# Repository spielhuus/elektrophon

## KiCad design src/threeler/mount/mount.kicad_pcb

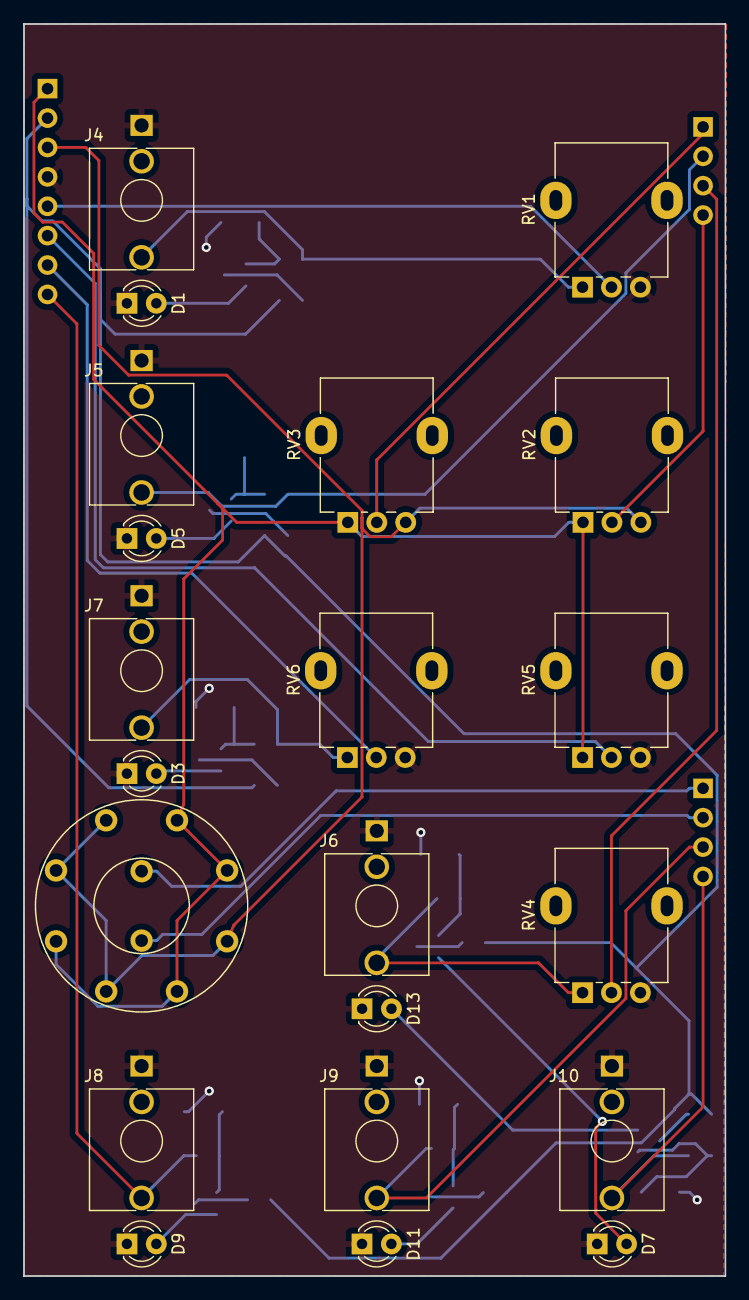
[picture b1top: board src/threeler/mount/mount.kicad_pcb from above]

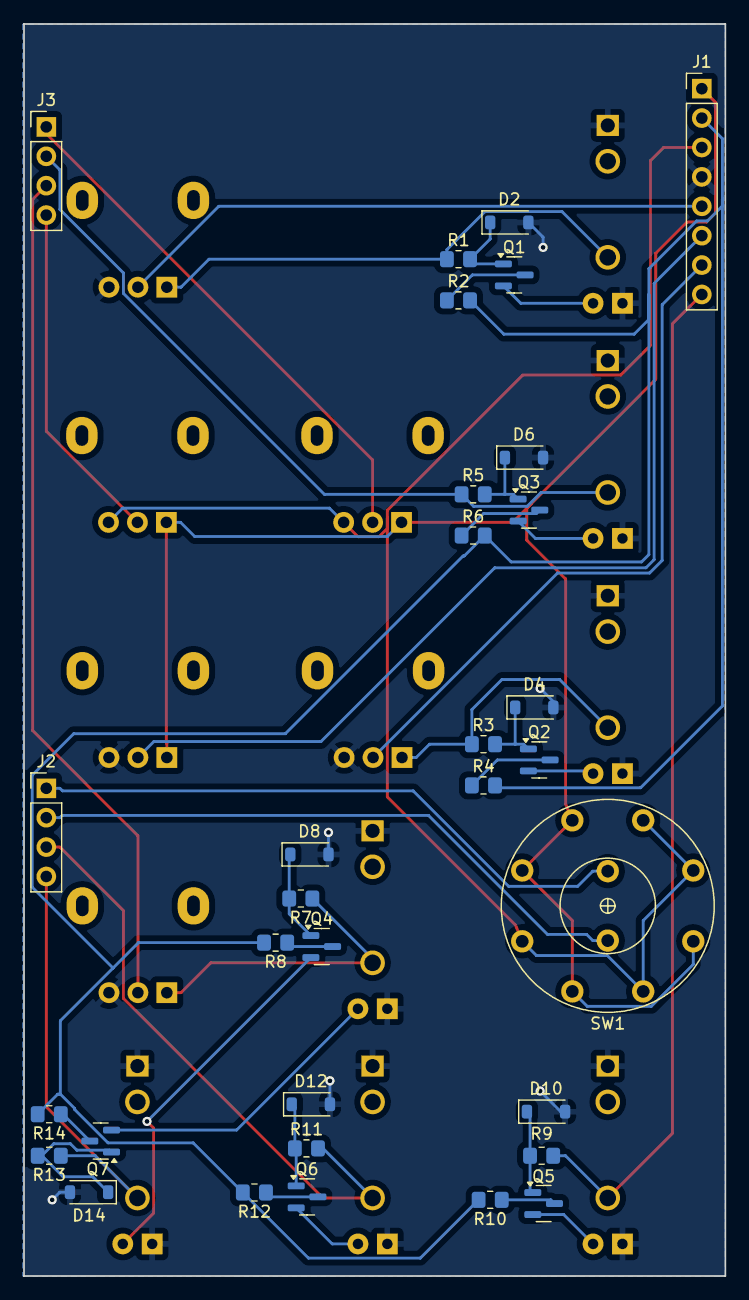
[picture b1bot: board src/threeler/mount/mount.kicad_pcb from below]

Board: 2 copper layers, 60.6 x 108.2 mm, 52 parts (31 on the bottom side), 40 nets.

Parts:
D1: LED (green); LED_D3.0mm
D2, D4, D6, D8, D10, D12, D14: 1N4148W; D_SOD-123
D3, D5, D7: LED (yellow); LED_D3.0mm
D9, D11, D13: LED (red); LED_D3.0mm
J1: Connector; PinHeader_1x08_P2.54mm_Vertical
J2, J3: Connector; PinHeader_1x04_P2.54mm_Vertical
J4, J5, J7: IN; Jack_3.5mm_WQP-PJ398SM_Vertical
J6: FM; Jack_3.5mm_WQP-PJ398SM_Vertical
J8, J9, J10: OUT; Jack_3.5mm_WQP-PJ398SM_Vertical
Q1, Q2, Q3, Q4, Q5, Q6, Q7: MMBT3904; SOT-23
R1, R3, R5, R7, R9, R11, R13: 100k; R_0805_2012Metric_Pad1.20x1.40mm_HandSolder
R2, R4, R6, R8, R10, R12, R14: 5.1k; R_0805_2012Metric_Pad1.20x1.40mm_HandSolder
RV1, RV2, RV3, RV4, RV5, RV6: 100k; Potentiometer_Alpha_RD901F-40-00D_Single_Vertical
SW1: 2P4T; 2P4T.MINI

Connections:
+5V: J1.2, R2.2, R4.2, R6.2, R8.2, R10.2, R12.2, R14.2
+15V: J1.1, RV2.1, RV3.1, RV5.1, SW1.2 (1), SW1.3 (2), SW1.7 (5), SW1.9 (7)
-15V: J1.3, RV2.3, RV3.3, SW1.4 (3), SW1.5 (4), SW1.8 (6), SW1.10 (8)
/A0: J2.1, SW1.1 (A)
/A1: J2.2, SW1.6 (B)
/COARSE: J3.4, RV2.2
/FINE: J3.1, RV3.2
/FM: J3.3, RV4.2
/FM_JACK: J6.T, R7.1, RV4.1
/IN: J1.5, RV1.2
/IN_JACK: J4.T, R1.1, RV1.1
/OUT_1: J1.8, J8.T, R9.1
/OUT_2: J2.3, J9.T, R11.1
/OUT_3: J2.4, J10.T, R13.1
/RES: J1.6, RV5.2
/RES_MOD: J1.7, RV6.2
/RES_MOD_JACK: J7.T, R3.1, RV6.1
/V/O: J3.2, J5.T, R5.1
GND: D1.1 (K), D2.2 (A), D3.1 (K), D4.2 (A), D5.1 (K), D6.2 (A), D7.1 (K), D8.2 (A), D9.1 (K), D10.2 (A), D11.1 (K), D12.2 (A), D13.1 (K), D14.2 (A), J1.4, J4.S, J5.S, J6.S, J7.S, J8.S, J9.S, J10.S, RV1.3, RV4.3, RV5.3, RV6.3
unnamed: D1.2 (A), Q1.2 (E)
unnamed: D2.1 (K), Q1.1 (B), R1.2
unnamed: D3.2 (A), Q2.2 (E)
unnamed: D4.1 (K), Q2.1 (B), R3.2
unnamed: D5.2 (A), Q3.2 (E)
unnamed: D6.1 (K), Q3.1 (B), R5.2
unnamed: D7.2 (A), Q4.2 (E)
unnamed: D8.1 (K), Q4.1 (B), R7.2
unnamed: D9.2 (A), Q5.2 (E)
unnamed: D10.1 (K), Q5.1 (B), R9.2
unnamed: D11.2 (A), Q6.2 (E)
unnamed: D12.1 (K), Q6.1 (B), R11.2
unnamed: D13.2 (A), Q7.2 (E)
unnamed: D14.1 (K), Q7.1 (B), R13.2
unnamed: Q1.3 (C), R2.1
unnamed: Q2.3 (C), R4.1
unnamed: Q3.3 (C), R6.1
unnamed: Q4.3 (C), R8.1
unnamed: Q5.3 (C), R10.1
unnamed: Q6.3 (C), R12.1
unnamed: Q7.3 (C), R14.1

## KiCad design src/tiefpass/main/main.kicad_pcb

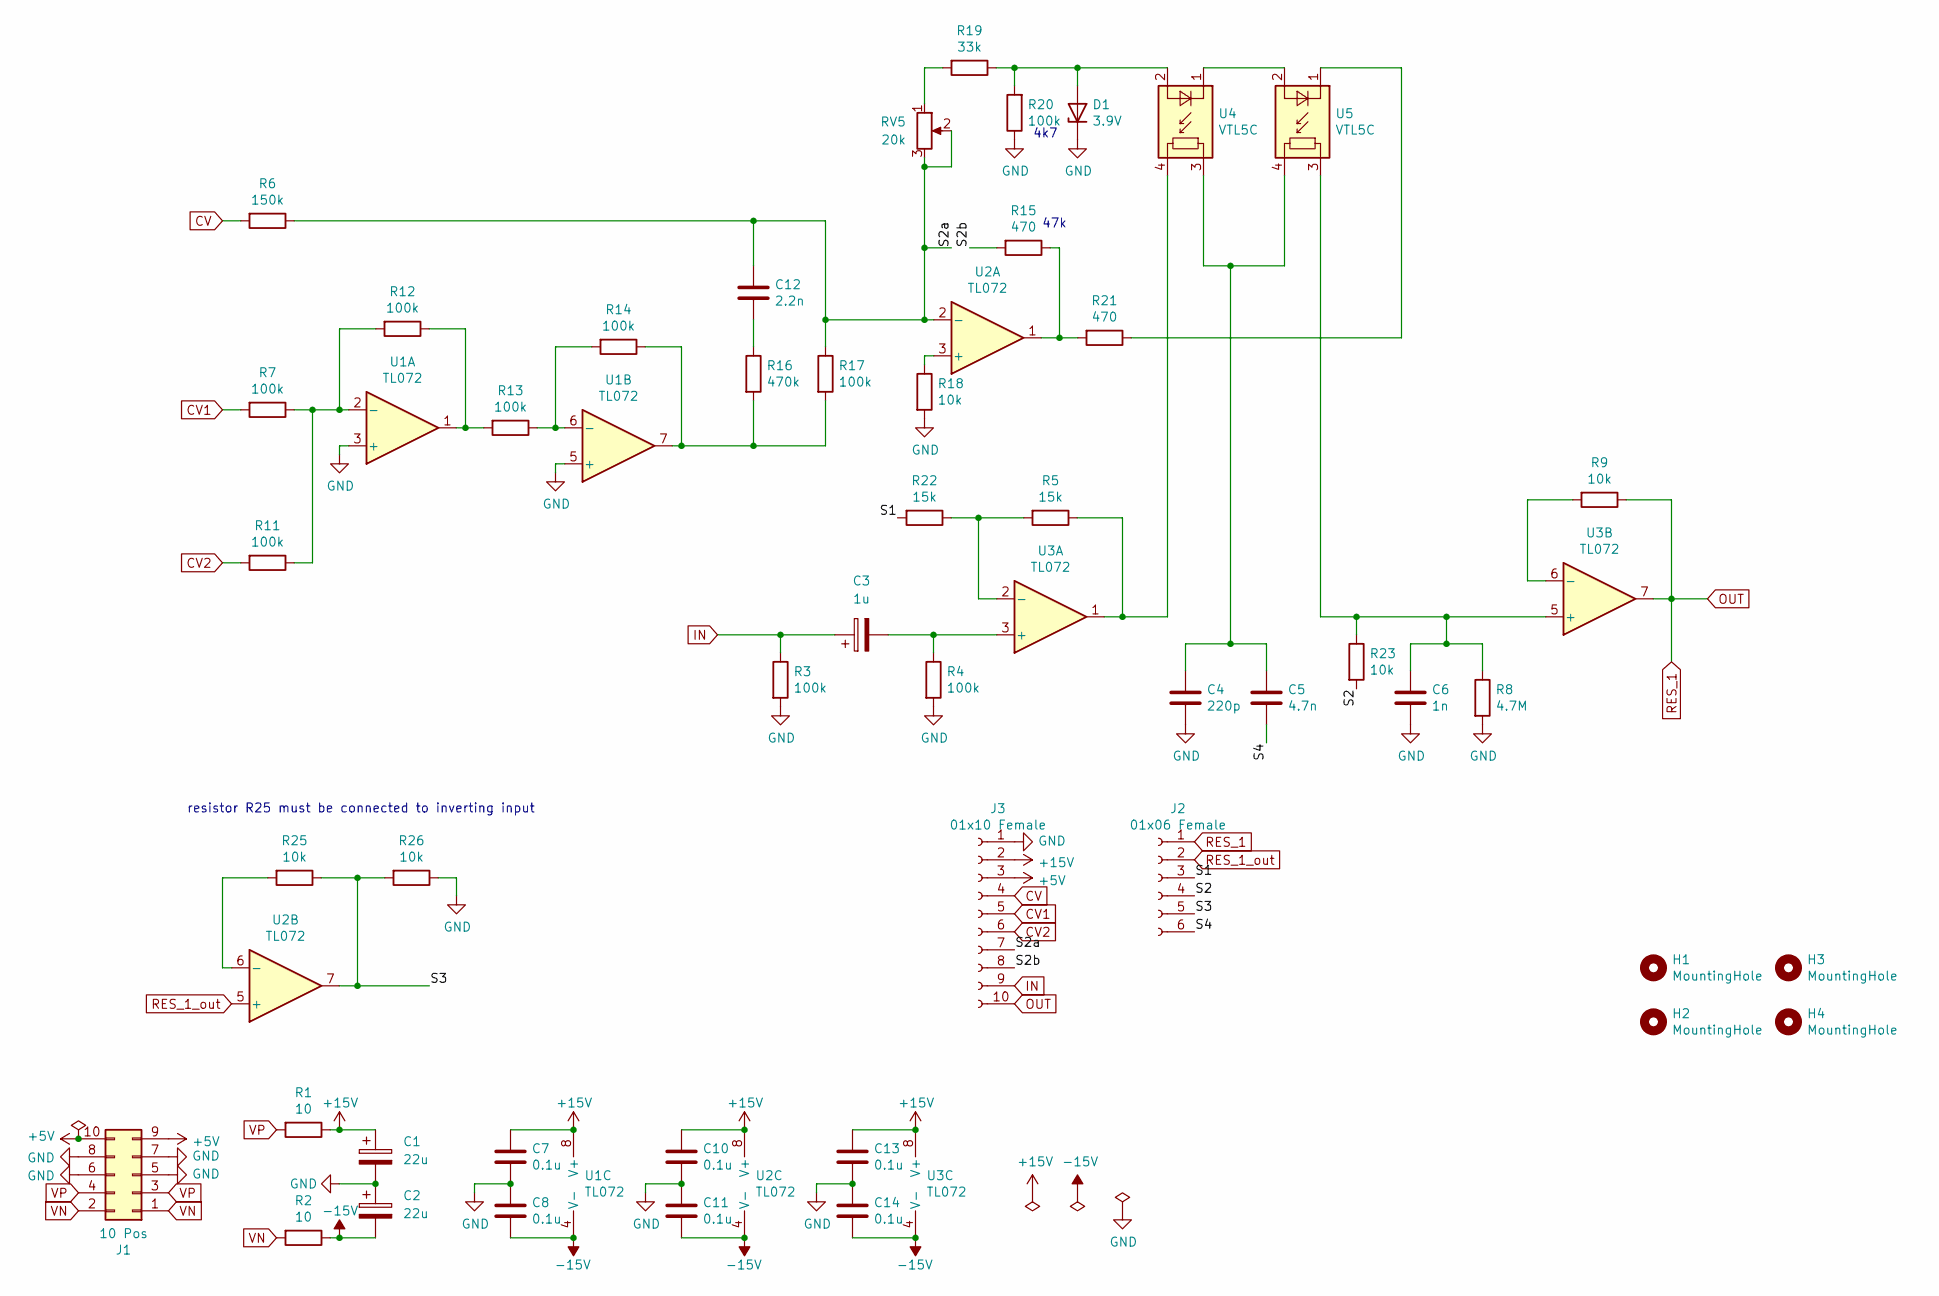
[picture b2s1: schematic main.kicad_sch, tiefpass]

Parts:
C1, C2: 22u; CP_Radial_D6.3mm_P2.50mm
C3: 1u; CP_Radial_D6.3mm_P2.50mm
C4: 220p; C_Rect_L7.2mm_W4.5mm_P5.00mm_FKS2_FKP2_MKS2_MKP2
C5: 4.7n; C_Rect_L7.2mm_W5.5mm_P5.00mm_FKS2_FKP2_MKS2_MKP2
C6: 1n; C_Rect_L7.2mm_W4.5mm_P5.00mm_FKS2_FKP2_MKS2_MKP2
C7, C8, C10, C11, C13, C14: 0.1u; C_Disc_D3.4mm_W2.1mm_P2.50mm
C12: 2.2n; C_Rect_L7.2mm_W4.5mm_P5.00mm_FKS2_FKP2_MKS2_MKP2
D1: 3.9V; D_DO-35_SOD27_P7.62mm_Horizontal
H1, H2, H3, H4: MountingHole; MountingHole_2.2mm_M2
J1: 10 Pos; IDC-Header_2x05_P2.54mm_Vertical
J2: 01x06 Female; PinSocket_1x06_P2.54mm_Vertical
J3: 01x10 Female; PinSocket_1x10_P2.54mm_Vertical
R1, R2: 10; R_Axial_DIN0204_L3.6mm_D1.6mm_P5.08mm_Horizontal
R3, R4, R7, R11, R12, R13, R14, R17, R20: 100k; R_Axial_DIN0204_L3.6mm_D1.6mm_P5.08mm_Horizontal
R5, R22: 15k; R_Axial_DIN0204_L3.6mm_D1.6mm_P5.08mm_Horizontal
R6: 150k; R_Axial_DIN0204_L3.6mm_D1.6mm_P5.08mm_Horizontal
R8: 4.7M; R_Axial_DIN0204_L3.6mm_D1.6mm_P5.08mm_Horizontal
R9, R18, R23, R25, R26: 10k; R_Axial_DIN0204_L3.6mm_D1.6mm_P5.08mm_Horizontal
R15, R21: 470; R_Axial_DIN0204_L3.6mm_D1.6mm_P5.08mm_Horizontal
R16: 470k; R_Axial_DIN0204_L3.6mm_D1.6mm_P5.08mm_Horizontal
R19: 33k; R_Axial_DIN0204_L3.6mm_D1.6mm_P5.08mm_Horizontal
RV5: 20k
U1, U2, U3: TL072; DIP-8_W7.62mm_Socket
U4, U5: VTL5C; PerkinElmer_VTL5C

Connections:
+5V: J1.9, J1.10, J3.3
+15V: C1.1, C7.1, C10.1, C13.1, J3.2, R1.1, U1.8 (V+), U2.8 (V+), U3.8 (V+)
-15V: C2.2, C8.2, C11.2, C14.2, R2.1, U1.4 (V-), U2.4 (V-), U3.4 (V-)
/S1: J2.3, R22.2
/S2: J2.4, R23.2
/S2a: C12.1, J3.7, R6.1, R17.1, RV5.2, RV5.3, U2.2 (-)
/S2b: J3.8, R15.2
/S3: J2.5, R25.1, R26.2, U2.7
/S4: C5.2, J2.6
CV: J3.4, R6.2
CV1: J3.5, R7.2
CV2: J3.6, R11.2
GND: C1.2, C2.1, C4.2, C6.2, C7.2, C8.1, C10.2, C11.1, C13.2, C14.1, D1.1 (K), J1.5, J1.6, J1.7, J1.8, J3.1, R3.2, R4.2, R8.2, R18.2, R20.1, R26.1, U1.3 (+), U1.5 (+)
IN: C3.1, J3.9, R3.1
unnamed: C3.2, R4.1, U3.3 (+)
unnamed: C4.1, C5.1, U4.3, U5.4
unnamed: C6.1, R8.1, R23.1, U3.5 (+), U5.3
unnamed: C12.2, R16.1
unnamed: D1.2 (A), R19.1, R20.2, U4.2 (+)
unnamed: R5.1, U3.1, U4.4
unnamed: R9.2, U3.6 (-)
unnamed: R7.1, R11.1, R12.2, U1.2 (-)
unnamed: R12.1, R13.2, U1.1
unnamed: R13.1, R14.2, U1.6 (-)
unnamed: R14.1, R16.2, R17.2, U1.7
unnamed: R15.1, R21.2, U2.1
unnamed: R18.1, U2.3 (+)
unnamed: R19.2, RV5.1
unnamed: R21.1, U5.1 (-)
unnamed: R5.2, R22.1, U3.2 (-)
unnamed: R25.2, U2.6 (-)
unnamed: U4.1 (-), U5.2 (+)
OUT: J2.1, J3.10, R9.1, U3.7
RES_1_out: J2.2, U2.5 (+)
VN: J1.1, J1.2, R2.2
VP: J1.3, J1.4, R1.2

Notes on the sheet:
resistor R25 must be connected to inverting input
47k
4k7

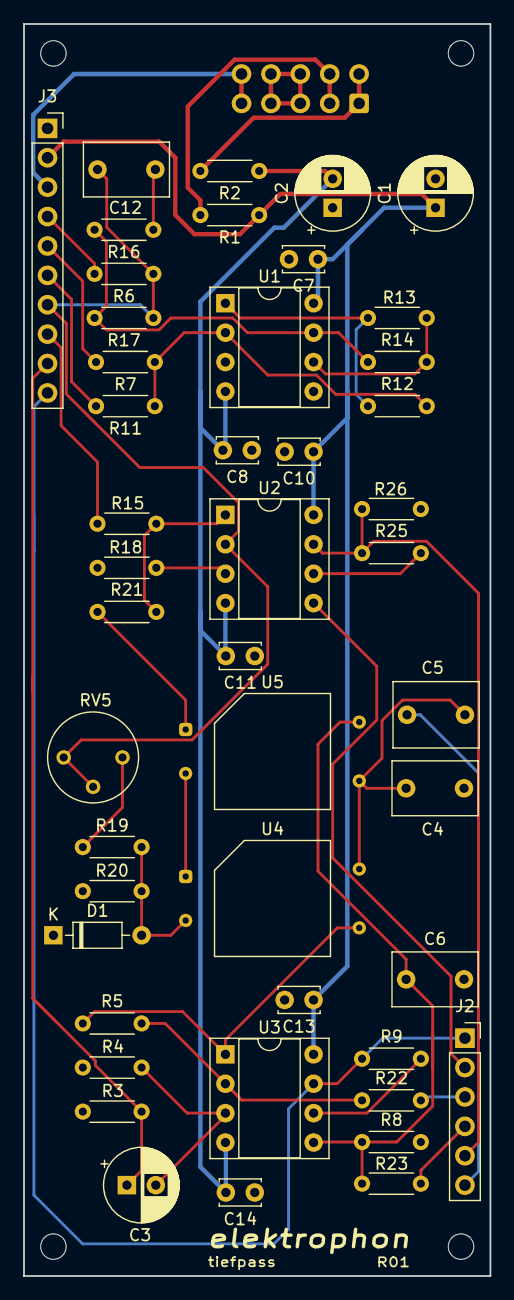
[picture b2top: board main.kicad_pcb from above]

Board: 2 copper layers, 40.3 x 108.2 mm, 51 parts (1 on the bottom side), 36 nets.

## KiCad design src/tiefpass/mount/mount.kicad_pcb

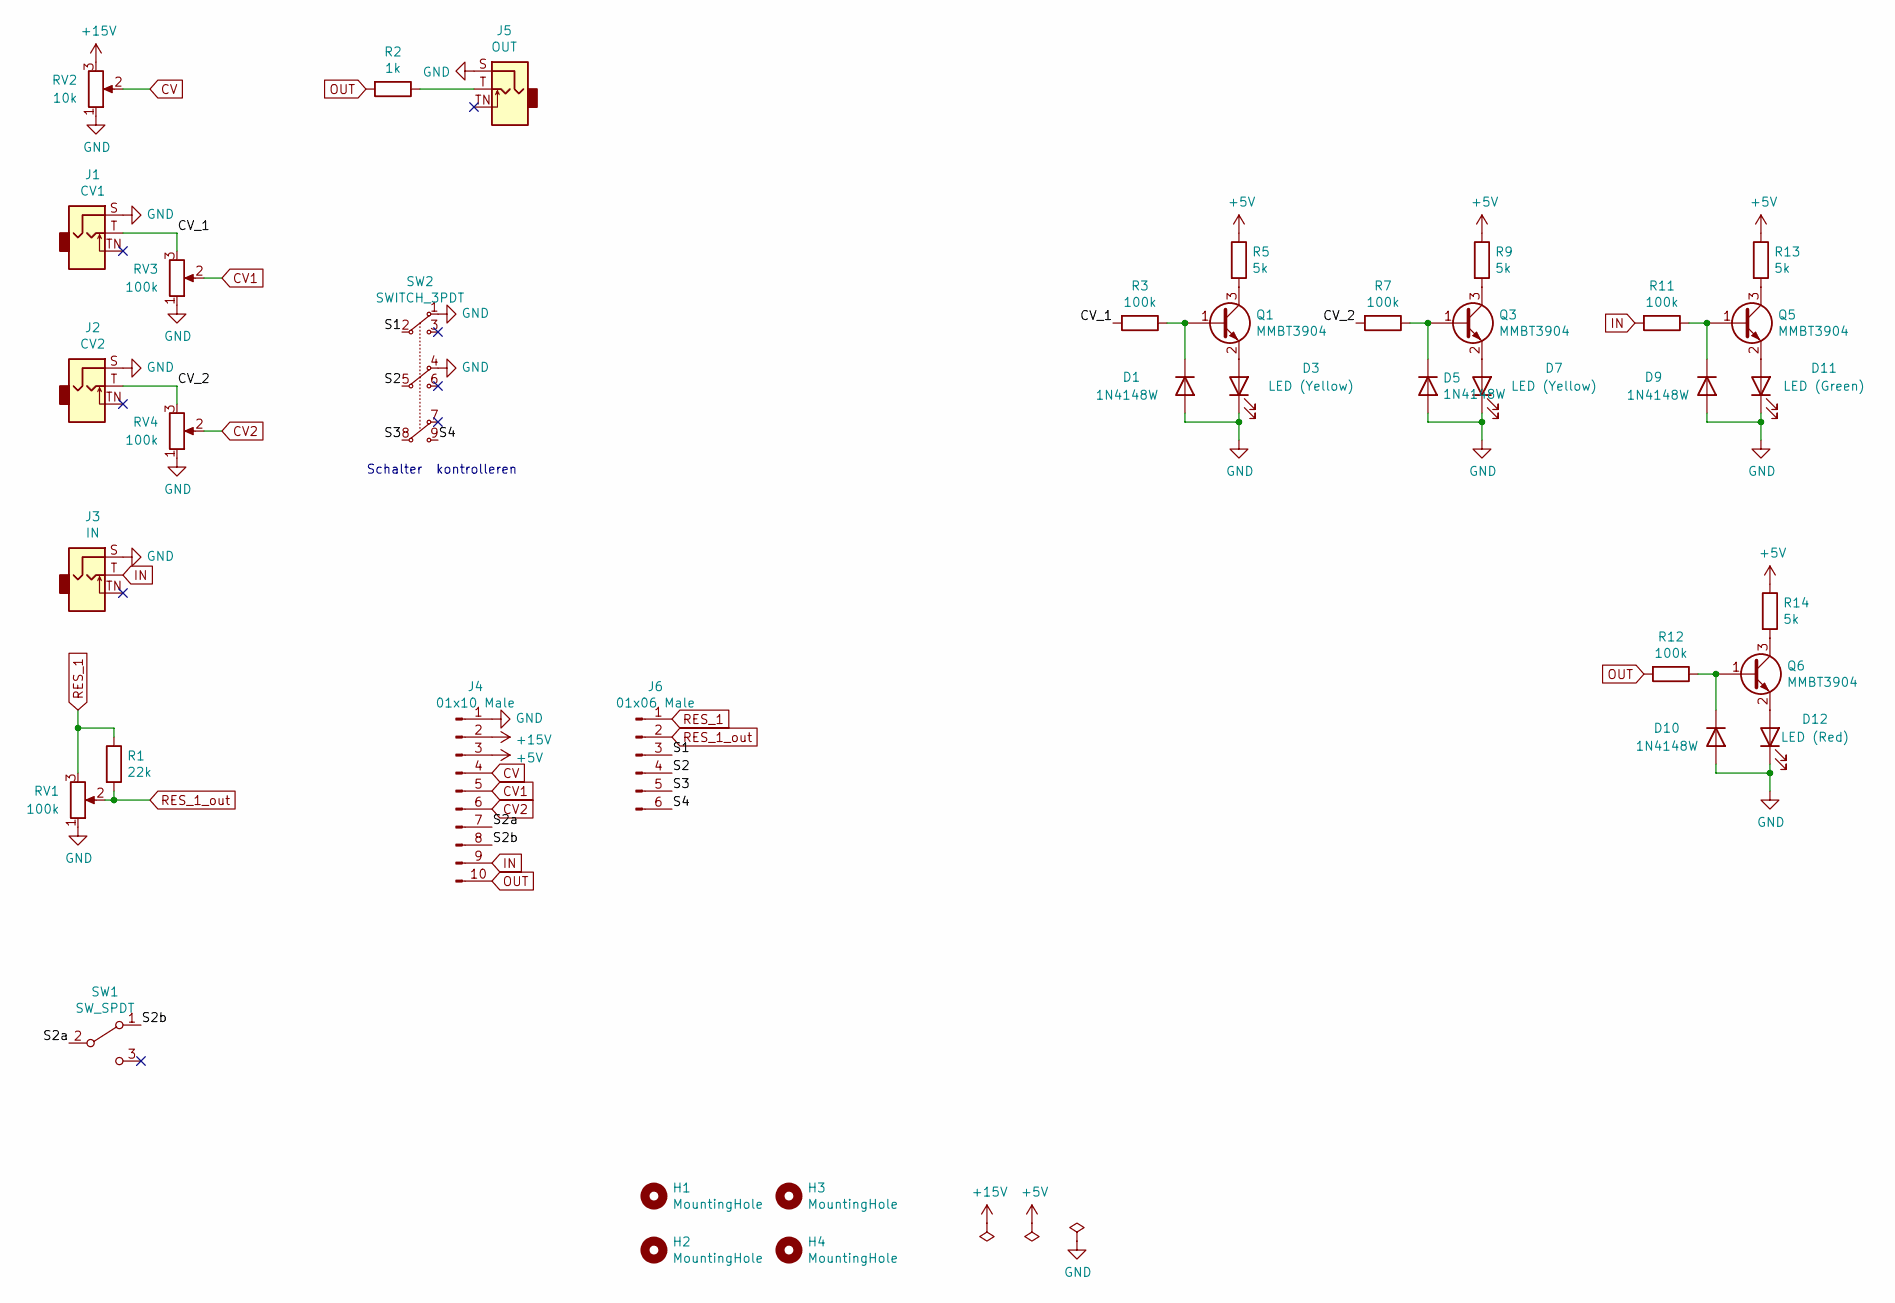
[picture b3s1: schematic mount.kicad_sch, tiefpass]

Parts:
D1, D5, D9, D10: 1N4148W; D_SOD-123
D3, D7: LED (Yellow); LED_D3.0mm
D11: LED (Green); LED_D3.0mm
D12: LED (Red); LED_D3.0mm
H1, H2, H3, H4: MountingHole; MountingHole_2.2mm_M2
J1: CV1; Jack_3.5mm_WQP-PJ398SM_Vertical
J2: CV2; Jack_3.5mm_WQP-PJ398SM_Vertical
J3: IN; Jack_3.5mm_WQP-PJ398SM_Vertical
J4: 01x10 Male; PinSocket_1x10_P2.54mm_Vertical
J5: OUT; Jack_3.5mm_WQP-PJ398SM_Vertical
J6: 01x06 Male; PinSocket_1x06_P2.54mm_Vertical
Q1, Q3, Q5, Q6: MMBT3904; SOT-23
R1: 22k; R_Axial_DIN0204_L3.6mm_D1.6mm_P5.08mm_Horizontal
R2: 1k; R_Axial_DIN0204_L3.6mm_D1.6mm_P5.08mm_Horizontal
R3, R7, R11, R12: 100k; R_0805_2012Metric_Pad1.20x1.40mm_HandSolder
R5, R9, R13, R14: 5k; R_0805_2012Metric_Pad1.20x1.40mm_HandSolder
RV1, RV3, RV4: 100k; Potentiometer_Alpha_RD901F-40-00D_Single_Vertical
RV2: 10k; Potentiometer_Alpha_RD901F-40-00D_Single_Vertical
SW1: SW_SPDT; SPDT_KIT
SW2: SWITCH_3PDT; 3PDT

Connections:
+5V: J4.3, R5.1, R9.1, R13.1, R14.1
+15V: J4.2, RV2.3
/CV_1: J1.T, R3.2, RV3.3
/CV_2: J2.T, R7.2, RV4.3
/S1: J6.3, SW2.2
/S2: J6.4, SW2.5
/S2a: J4.7, SW1.2 (B)
/S2b: J4.8, SW1.1 (A)
/S3: J6.5, SW2.8
/S4: J6.6, SW2.9
CV: J4.4, RV2.2
CV1: J4.5, RV3.2
CV2: J4.6, RV4.2
GND: D1.2 (A), D3.1 (K), D5.2 (A), D7.1 (K), D9.2 (A), D10.2 (A), D11.1 (K), D12.1 (K), J1.S, J2.S, J3.S, J4.1, J5.S, RV1.1, RV2.1, RV3.1, RV4.1, SW2.1, SW2.4
IN: J3.T, J4.9, R11.2
unnamed: D1.1 (K), Q1.1 (B), R3.1
unnamed: D3.2 (A), Q1.2 (E)
unnamed: D5.1 (K), Q3.1 (B), R7.1
unnamed: D7.2 (A), Q3.2 (E)
unnamed: D9.1 (K), Q5.1 (B), R11.1
unnamed: D10.1 (K), Q6.1 (B), R12.1
unnamed: D11.2 (A), Q5.2 (E)
unnamed: D12.2 (A), Q6.2 (E)
unnamed: J5.T, R2.1
unnamed: Q1.3 (C), R5.2
unnamed: Q3.3 (C), R9.2
unnamed: Q5.3 (C), R13.2
unnamed: Q6.3 (C), R14.2
OUT: J4.10, R2.2, R12.2
RES_1: J6.1, R1.1, RV1.3
RES_1_out: J6.2, R1.2, RV1.2

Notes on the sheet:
Schalter kontrolleren

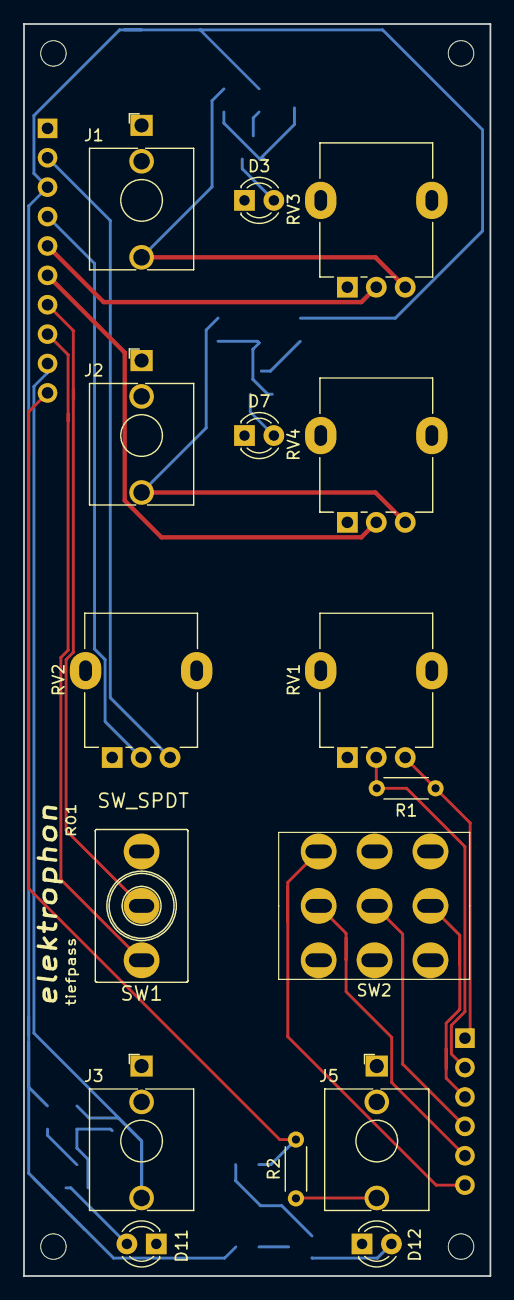
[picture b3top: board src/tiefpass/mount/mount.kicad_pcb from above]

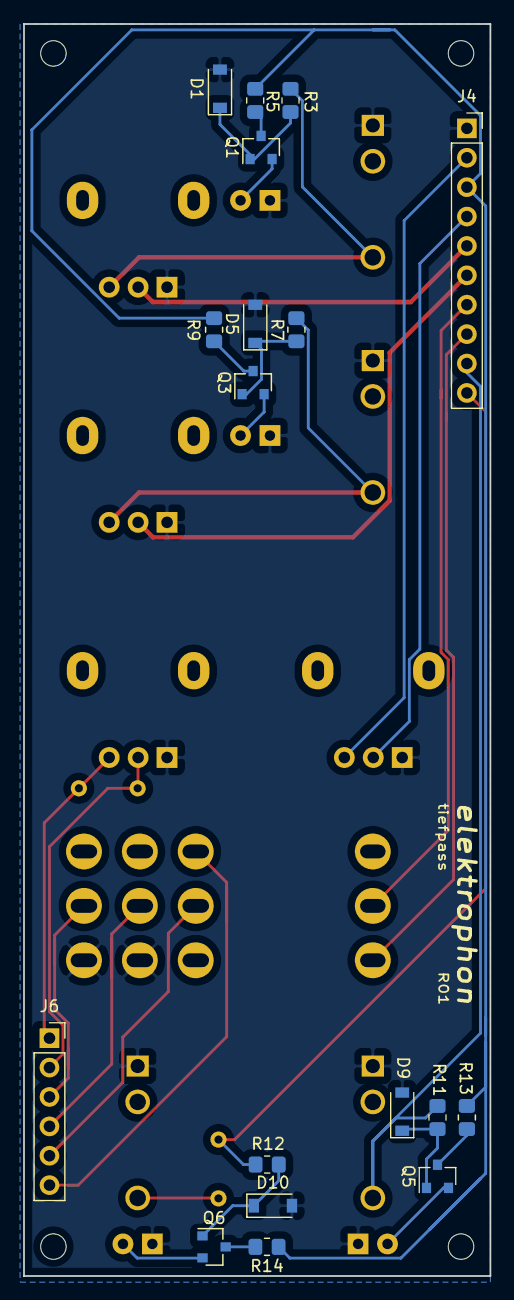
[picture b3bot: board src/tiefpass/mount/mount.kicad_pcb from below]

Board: 2 copper layers, 40.3 x 108.2 mm, 38 parts (18 on the bottom side), 31 nets.

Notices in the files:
src/ssg/main/main.kicad_sch:
License CC BY 4.0 - Attribution 4.0 International
